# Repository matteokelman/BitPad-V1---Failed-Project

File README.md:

# BitPad-V1---Failed-Project
So this project was meant to be a MacroPad in a retro style with 9 keys and 2 rotary dials, however this was to ambitious for a new hack-clubber with 0 PCB and KiCad knowledge so I am ending the project here to claim my hours of work that went into the project.

Sad to see this project fail but I hope I can do better next time.

Error Report: ** Drc report for MacroPAD.kicad_pcb **
** Created on 2026-10-27T22:11:03 **
** Report includes: Errors, Warnings **
** Found 106 DRC violations **
[shorting_items]: Items shorting two nets (nets Net-(D9-A) and R1)
Local override; error
@(154.7200 mm, 88.9100 mm): Track [Net-(D9-A)] on B.Cu, length 1.9900 mm
@(154.7000 mm, 86.2000 mm): PTH pad 1 [R1] of D1
[shorting_items]: Items shorting two nets (nets Net-(D9-A) and R1)
Local override; error
@(192.8200 mm, 86.9200 mm): Track [Net-(D9-A)] on B.Cu, length 0.0283 mm
@(192.8000 mm, 86.2000 mm): PTH pad 1 [R1] of D3
[shorting_items]: Items shorting two nets (nets R2 and Net-(D9-A))
Local override; error
@(173.7500 mm, 105.2500 mm): PTH pad 1 [R2] of D5
@(173.7700 mm, 105.9700 mm): Track [Net-(D9-A)] on B.Cu, length 0.0283 mm
[shorting_items]: Items shorting two nets (nets R2 and Net-(D9-A))
Local override; error
@(154.7000 mm, 105.2500 mm): PTH pad 1 [R2] of D4
@(154.7200 mm, 107.9600 mm): Track [Net-(D9-A)] on B.Cu, length 1.9900 mm
[shorting_items]: Items shorting two nets (nets R2 and Net-(D9-A))
Local override; error
@(192.8000 mm, 105.2500 mm): PTH pad 1 [R2] of D6
@(192.8200 mm, 107.9600 mm): Track [Net-(D9-A)] on B.Cu, length 1.9900 mm
[shorting_items]: Items shorting two nets (nets Net-(D9-A) and R1)
Local override; error
@(192.8200 mm, 88.9100 mm): Track [Net-(D9-A)] on B.Cu, length 1.9900 mm
@(192.8000 mm, 86.2000 mm): PTH pad 1 [R1] of D3
[shorting_items]: Items shorting two nets (nets R3 and Net-(D9-A))
Local override; error
@(154.7000 mm, 124.3000 mm): PTH pad 1 [R3] of D7
@(154.7200 mm, 125.0200 mm): Track [Net-(D9-A)] on B.Cu, length 0.0283 mm
[shorting_items]: Items shorting two nets (nets R1 and Net-(D9-A))
Local override; error
@(173.7500 mm, 86.2000 mm): PTH pad 1 [R1] of D2
@(173.7700 mm, 86.9200 mm): Track [Net-(D9-A)] on B.Cu, length 0.0283 mm
[shorting_items]: Items shorting two nets (nets R3 and Net-(D9-A))
Local override; error
@(173.7500 mm, 124.3000 mm): PTH pad 1 [R3] of D8
@(173.7700 mm, 127.0100 mm): Track [Net-(D9-A)] on B.Cu, length 1.9900 mm
[shorting_items]: Items shorting two nets (nets Net-(D9-A) and R1)
Local override; error
@(154.7200 mm, 86.9200 mm): Track [Net-(D9-A)] on B.Cu, length 0.0283 mm
@(154.7000 mm, 86.2000 mm): PTH pad 1 [R1] of D1
[shorting_items]: Items shorting two nets (nets R2 and Net-(D9-A))
Local override; error
@(192.8000 mm, 105.2500 mm): PTH pad 1 [R2] of D6
@(192.8200 mm, 105.9700 mm): Track [Net-(D9-A)] on B.Cu, length 0.0283 mm
[shorting_items]: Items shorting two nets (nets Net-(D9-A) and R1)
Local override; error
@(173.7700 mm, 88.9100 mm): Track [Net-(D9-A)] on B.Cu, length 1.9900 mm
@(173.7500 mm, 86.2000 mm): PTH pad 1 [R1] of D2
[shorting_items]: Items shorting two nets (nets R3 and Net-(D9-A))
Local override; error
@(173.7500 mm, 124.3000 mm): PTH pad 1 [R3] of D8
@(173.7700 mm, 125.0200 mm): Track [Net-(D9-A)] on B.Cu, length 0.0283 mm
[shorting_items]: Items shorting two nets (nets Net-(D9-A) and R3)
Local override; error
@(154.7200 mm, 127.0100 mm): Track [Net-(D9-A)] on B.Cu, length 1.9900 mm
@(154.7000 mm, 124.3000 mm): PTH pad 1 [R3] of D7
[shorting_items]: Items shorting two nets (nets Net-(D9-A) and R3)
Local override; error
@(192.8200 mm, 125.0200 mm): Track [Net-(D9-A)] on B.Cu, length 0.0283 mm
@(192.8000 mm, 124.3000 mm): PTH pad 1 [R3] of D9
[shorting_items]: Items shorting two nets (nets R2 and Net-(D9-A))
Local override; error
@(173.7500 mm, 105.2500 mm): PTH pad 1 [R2] of D5
@(173.7700 mm, 107.9600 mm): Track [Net-(D9-A)] on B.Cu, length 1.9900 mm
[shorting_items]: Items shorting two nets (nets R2 and Net-(D9-A))
Local override; error
@(154.7000 mm, 105.2500 mm): PTH pad 1 [R2] of D4
@(154.7200 mm, 105.9700 mm): Track [Net-(D9-A)] on B.Cu, length 0.0283 mm
[shorting_items]: Items shorting two nets (nets Net-(D9-A) and R3)
Local override; error
@(192.8200 mm, 127.0100 mm): Track [Net-(D9-A)] on B.Cu, length 1.9900 mm
@(192.8000 mm, 124.3000 mm): PTH pad 1 [R3] of D9
[copper_edge_clearance]: Board edge clearance violation (board setup constraints edge clearance 0.1500 mm; actual 0.0040 mm)
Rule: board setup constraints edge; error
@(178.8490 mm, 134.9394 mm): Arc of D11 on Edge.Cuts
@(180.1500 mm, 134.5528 mm): Pad 1 [5V] of D11 on B.Cu
[copper_edge_clearance]: Board edge clearance violation (board setup constraints edge clearance 0.1500 mm; actual 0.0040 mm)
Rule: board setup constraints edge; error
@(178.8490 mm, 132.6662 mm): Arc of D11 on Edge.Cuts
@(180.1500 mm, 133.0528 mm): Pad 2 [Net-(D10-DOUT)] of D11 on B.Cu
[copper_edge_clearance]: Board edge clearance violation (board setup constraints edge clearance 0.1500 mm; actual 0.1244 mm)
Rule: board setup constraints edge; error
@(175.3500 mm, 133.1000 mm): Arc of D11 on Edge.Cuts
@(174.9500 mm, 133.0528 mm): Pad 3 [GND] of D11 on B.Cu
[copper_edge_clearance]: Board edge clearance violation (board setup constraints edge clearance 0.1500 mm; actual 0.1244 mm)
Rule: board setup constraints edge; error
@(175.3500 mm, 134.5057 mm): Arc of D11 on Edge.Cuts
@(174.9500 mm, 134.5528 mm): Pad 4 [Net-(D10-DOUT)] of D11 on B.Cu
[copper_edge_clearance]: Board edge clearance violation (board setup constraints edge clearance 0.1500 mm; actual 0.1000 mm)
Rule: board setup constraints edge; error
@(160.2000 mm, 95.0000 mm): Segment of D18 on Edge.Cuts
@(161.1000 mm, 96.4528 mm): Pad 1 [5V] of D18 on B.Cu
[copper_edge_clearance]: Board edge clearance violation (board setup constraints edge clearance 0.1500 mm; actual 0.1000 mm)
Rule: board setup constraints edge; error
@(160.2000 mm, 95.0000 mm): Segment of D18 on Edge.Cuts
@(161.1000 mm, 94.9528 mm): Pad 2 [Net-(D10-DOUT)] of D18 on B.Cu
[copper_edge_clearance]: Board edge clearance violation (board setup constraints edge clearance 0.1500 mm; actual 0.1244 mm)
Rule: board setup constraints edge; error
@(156.3000 mm, 95.0000 mm): Arc of D18 on Edge.Cuts
@(155.9000 mm, 94.9528 mm): Pad 3 [GND] of D18 on B.Cu
[copper_edge_clearance]: Board edge clearance violation (board setup constraints edge clearance 0.1500 mm; actual 0.1000 mm)
Rule: board setup constraints edge; error
@(156.8000 mm, 96.4057 mm): Segment of D18 on Edge.Cuts
@(155.9000 mm, 96.4528 mm): Pad 4 [Net-(D10-DIN)] of D18 on B.Cu
[copper_edge_clearance]: Board edge clearance violation (board setup constraints edge clearance 0.1500 mm; actual 0.1000 mm)
Rule: board setup constraints edge; error
@(198.3000 mm, 133.1000 mm): Segment of D10 on Edge.Cuts
@(199.2000 mm, 134.5528 mm): Pad 1 [5V] of D10 on B.Cu
[copper_edge_clearance]: Board edge clearance violation (board setup constraints edge clearance 0.1500 mm; actual 0.1000 mm)
Rule: board setup constraints edge; error
@(198.3000 mm, 133.1000 mm): Segment of D10 on Edge.Cuts
@(199.2000 mm, 133.0528 mm): Pad 2 [Net-(D10-DOUT)] of D10 on B.Cu
[copper_edge_clearance]: Board edge clearance violation (board setup constraints edge clearance 0.1500 mm; actual 0.1000 mm)
Rule: board setup constraints edge; error
@(194.9000 mm, 134.5057 mm): Segment of D10 on Edge.Cuts
@(194.0000 mm, 133.0528 mm): Pad 3 [GND] of D10 on B.Cu
[copper_edge_clearance]: Board edge clearance violation (board setup constraints edge clearance 0.1500 mm; actual 0.1000 mm)
Rule: board setup constraints edge; error
@(194.9000 mm, 134.5057 mm): Segment of D10 on Edge.Cuts
@(194.0000 mm, 134.5528 mm): Pad 4 [Net-(D10-DOUT)] of D10 on B.Cu
[copper_edge_clearance]: Board edge clearance violation (board setup constraints edge clearance 0.1500 mm; actual 0.1000 mm)
Rule: board setup constraints edge; error
@(156.8000 mm, 115.6000 mm): Segment of D13 on Edge.Cuts
@(155.9000 mm, 114.1472 mm): Pad 1 [5V] of D13 on B.Cu
[copper_edge_clearance]: Board edge clearance violation (board setup constraints edge clearance 0.1500 mm; actual 0.1244 mm)
Rule: board setup constraints edge; error
@(156.3000 mm, 115.6000 mm): Arc of D13 on Edge.Cuts
@(155.9000 mm, 115.6472 mm): Pad 2 [Net-(D10-DOUT)] of D13 on B.Cu
[copper_edge_clearance]: Board edge clearance violation (board setup constraints edge clearance 0.1500 mm; actual 0.0040 mm)
Rule: board setup constraints edge; error
@(159.7990 mm, 116.0338 mm): Arc of D13 on Edge.Cuts
@(161.1000 mm, 115.6472 mm): Pad 3 [GND] of D13 on B.Cu
[copper_edge_clearance]: Board edge clearance violation (board setup constraints edge clearance 0.1500 mm; actual 0.1000 mm)
Rule: board setup constraints edge; error
@(160.2000 mm, 114.1943 mm): Segment of D13 on Edge.Cuts
@(161.1000 mm, 114.1472 mm): Pad 4 [Net-(D10-DOUT)] of D13 on B.Cu
[copper_edge_clearance]: Board edge clearance violation (board setup constraints edge clearance 0.1500 mm; actual 0.0040 mm)
Rule: board setup constraints edge; error
@(197.8990 mm, 96.8394 mm): Arc of D16 on Edge.Cuts
@(199.2000 mm, 96.4528 mm): Pad 1 [5V] of D16 on B.Cu
[copper_edge_clearance]: Board edge clearance violation (board setup constraints edge clearance 0.1500 mm; actual 0.1244 mm)
Rule: board setup constraints edge; error
@(198.8000 mm, 95.0000 mm): Arc of D16 on Edge.Cuts
@(199.2000 mm, 94.9528 mm): Pad 2 [Net-(D10-DOUT)] of D16 on B.Cu
[copper_edge_clearance]: Board edge clearance violation (board setup constraints edge clearance 0.1500 mm; actual 0.0040 mm)
Rule: board setup constraints edge; error
@(195.3010 mm, 94.5662 mm): Arc of D16 on Edge.Cuts
@(194.0000 mm, 94.9528 mm): Pad 3 [GND] of D16 on B.Cu
[copper_edge_clearance]: Board edge clearance violation (board setup constraints edge clearance 0.1500 mm; actual 0.1244 mm)
Rule: board setup constraints edge; error
@(194.4000 mm, 96.4057 mm): Arc of D16 on Edge.Cuts
@(194.0000 mm, 96.4528 mm): Pad 4 [Net-(D10-DOUT)] of D16 on B.Cu
[copper_edge_clearance]: Board edge clearance violation (board setup constraints edge clearance 0.1500 mm; actual 0.0040 mm)
Rule: board setup constraints edge; error
@(159.7990 mm, 134.9394 mm): Arc of D12 on Edge.Cuts
@(161.1000 mm, 134.5528 mm): Pad 1 [5V] of D12 on B.Cu
[copper_edge_clearance]: Board edge clearance violation (board setup constraints edge clearance 0.1500 mm; actual 0.1000 mm)
Rule: board setup constraints edge; error
@(160.2000 mm, 133.1000 mm): Segment of D12 on Edge.Cuts
@(161.1000 mm, 133.0528 mm): Pad 2 [Net-(D10-DOUT)] of D12 on B.Cu
[copper_edge_clearance]: Board edge clearance violation (board setup constraints edge clearance 0.1500 mm; actual 0.1000 mm)
Rule: board setup constraints edge; error
@(156.8000 mm, 134.5057 mm): Segment of D12 on Edge.Cuts
@(155.9000 mm, 133.0528 mm): Pad 3 [GND] of D12 on B.Cu
[copper_edge_clearance]: Board edge clearance violation (board setup constraints edge clearance 0.1500 mm; actual 0.1000 mm)
Rule: board setup constraints edge; error
@(156.8000 mm, 134.5057 mm): Segment of D12 on Edge.Cuts
@(155.9000 mm, 134.5528 mm): Pad 4 [Net-(D10-DOUT)] of D12 on B.Cu
[copper_edge_clearance]: Board edge clearance violation (board setup constraints edge clearance 0.1500 mm; actual 0.0040 mm)
Rule: board setup constraints edge; error
@(178.8490 mm, 96.8394 mm): Arc of D17 on Edge.Cuts
@(180.1500 mm, 96.4528 mm): Pad 1 [5V] of D17 on B.Cu
[copper_edge_clearance]: Board edge clearance violation (board setup constraints edge clearance 0.1500 mm; actual 0.1000 mm)
Rule: board setup constraints edge; error
@(179.2500 mm, 95.0000 mm): Segment of D17 on Edge.Cuts
@(180.1500 mm, 94.9528 mm): Pad 2 [Net-(D10-DOUT)] of D17 on B.Cu
[copper_edge_clearance]: Board edge clearance violation (board setup constraints edge clearance 0.1500 mm; actual 0.1000 mm)
Rule: board setup constraints edge; error
@(175.8500 mm, 96.4057 mm): Segment of D17 on Edge.Cuts
@(174.9500 mm, 94.9528 mm): Pad 3 [GND] of D17 on B.Cu
[copper_edge_clearance]: Board edge clearance violation (board setup constraints edge clearance 0.1500 mm; actual 0.1244 mm)
Rule: board setup constraints edge; error
@(175.3500 mm, 96.4057 mm): Arc of D17 on Edge.Cuts
@(174.9500 mm, 96.4528 mm): Pad 4 [Net-(D10-DOUT)] of D17 on B.Cu
[copper_edge_clearance]: Board edge clearance violation (board setup constraints edge clearance 0.1500 mm; actual 0.1000 mm)
Rule: board setup constraints edge; error
@(194.9000 mm, 115.6000 mm): Segment of D15 on Edge.Cuts
@(194.0000 mm, 114.1472 mm): Pad 1 [5V] of D15 on B.Cu
[copper_edge_clearance]: Board edge clearance violation (board setup constraints edge clearance 0.1500 mm; actual 0.1000 mm)
Rule: board setup constraints edge; error
@(194.9000 mm, 115.6000 mm): Segment of D15 on Edge.Cuts
@(194.0000 mm, 115.6472 mm): Pad 2 [Net-(D10-DOUT)] of D15 on B.Cu
[copper_edge_clearance]: Board edge clearance violation (board setup constraints edge clearance 0.1500 mm; actual 0.0040 mm)
Rule: board setup constraints edge; error
@(197.8990 mm, 116.0338 mm): Arc of D15 on Edge.Cuts
@(199.2000 mm, 115.6472 mm): Pad 3 [GND] of D15 on B.Cu
[copper_edge_clearance]: Board edge clearance violation (board setup constraints edge clearance 0.1500 mm; actual 0.0039 mm)
Rule: board setup constraints edge; error
@(197.8990 mm, 113.7606 mm): Arc of D15 on Edge.Cuts
@(199.2000 mm, 114.1472 mm): Pad 4 [Net-(D10-DOUT)] of D15 on B.Cu
[copper_edge_clearance]: Board edge clearance violation (board setup constraints edge clearance 0.1500 mm; actual 0.0040 mm)
Rule: board setup constraints edge; error
@(176.2510 mm, 113.7606 mm): Arc of D14 on Edge.Cuts
@(174.9500 mm, 114.1472 mm): Pad 1 [5V] of D14 on B.Cu
[copper_edge_clearance]: Board edge clearance violation (board setup constraints edge clearance 0.1500 mm; actual 0.1000 mm)
Rule: board setup constraints edge; error
@(175.8500 mm, 115.6000 mm): Segment of D14 on Edge.Cuts
@(174.9500 mm, 115.6472 mm): Pad 2 [Net-(D10-DOUT)] of D14 on B.Cu
[copper_edge_clearance]: Board edge clearance violation (board setup constraints edge clearance 0.1500 mm; actual 0.1000 mm)
Rule: board setup constraints edge; error
@(179.2500 mm, 114.1943 mm): Segment of D14 on Edge.Cuts
@(180.1500 mm, 115.6472 mm): Pad 3 [GND] of D14 on B.Cu
[copper_edge_clearance]: Board edge clearance violation (board setup constraints edge clearance 0.1500 mm; actual 0.0039 mm)
Rule: board setup constraints edge; error
@(178.8490 mm, 113.7606 mm): Arc of D14 on Edge.Cuts
@(180.1500 mm, 114.1472 mm): Pad 4 [Net-(D10-DOUT)] of D14 on B.Cu
[starved_thermal]: Thermal relief connection to zone incomplete (layer B.Cu; zone min spoke count 2; actual 1)
Local override; error
@(103.0000 mm, 58.0000 mm): Zone [GND] on B.Cu, priority 0
@(161.1000 mm, 115.6472 mm): Pad 3 [GND] of D13 on B.Cu
[starved_thermal]: Thermal relief connection to zone incomplete (layer B.Cu; zone min spoke count 2; actual 1)
Local override; error
@(103.0000 mm, 58.0000 mm): Zone [GND] on B.Cu, priority 0
@(180.1500 mm, 115.6472 mm): Pad 3 [GND] of D14 on B.Cu
[solder_mask_bridge]: Rear solder mask aperture bridges items with different nets
Rule: board setup solder mask min width; error
@(173.7700 mm, 88.9100 mm): Track [Net-(D9-A)] on B.Cu, length 1.9900 mm
@(173.7500 mm, 86.2000 mm): PTH pad 1 [R1] of D2
[solder_mask_bridge]: Rear solder mask aperture bridges items with different nets
Rule: board setup solder mask min width; error
@(192.8200 mm, 127.0100 mm): Track [Net-(D9-A)] on B.Cu, length 1.9900 mm
@(192.8000 mm, 124.3000 mm): PTH pad 1 [R3] of D9
[solder_mask_bridge]: Rear solder mask aperture bridges items with different nets
Rule: board setup solder mask min width; error
@(173.7700 mm, 125.0200 mm): Track [Net-(D9-A)] on B.Cu, length 0.0283 mm
@(173.7500 mm, 124.3000 mm): PTH pad 1 [R3] of D8
[solder_mask_bridge]: Rear solder mask aperture bridges items with different nets
Rule: board setup solder mask min width; error
@(192.8200 mm, 125.0200 mm): Track [Net-(D9-A)] on B.Cu, length 0.0283 mm
@(192.8000 mm, 124.3000 mm): PTH pad 1 [R3] of D9
[solder_mask_bridge]: Rear solder mask aperture bridges items with different nets
Rule: board setup solder mask min width; error
@(154.7200 mm, 88.9100 mm): Track [Net-(D9-A)] on B.Cu, length 1.9900 mm
@(154.7000 mm, 86.2000 mm): PTH pad 1 [R1] of D1
[solder_mask_bridge]: Rear solder mask aperture bridges items with different nets
Rule: board setup solder mask min width; error
@(154.7200 mm, 105.9700 mm): Track [Net-(D9-A)] on B.Cu, length 0.0283 mm
@(154.7000 mm, 105.2500 mm): PTH pad 1 [R2] of D4
[solder_mask_bridge]: Rear solder mask aperture bridges items with different nets
Rule: board setup solder mask min width; error
@(192.8200 mm, 86.9200 mm): Track [Net-(D9-A)] on B.Cu, length 0.0283 mm
@(192.8000 mm, 86.2000 mm): PTH pad 1 [R1] of D3
[solder_mask_bridge]: Rear solder mask aperture bridges items with different nets
Rule: board setup solder mask min width; error
@(173.7700 mm, 107.9600 mm): Track [Net-(D9-A)] on B.Cu, length 1.9900 mm
@(173.7500 mm, 105.2500 mm): PTH pad 1 [R2] of D5
[solder_mask_bridge]: Rear solder mask aperture bridges items with different nets
Rule: board setup solder mask min width; error
@(173.7700 mm, 127.0100 mm): Track [Net-(D9-A)] on B.Cu, length 1.9900 mm
@(173.7500 mm, 124.3000 mm): PTH pad 1 [R3] of D8
[solder_mask_bridge]: Rear solder mask aperture bridges items with different nets
Rule: board setup solder mask min width; error
@(192.8200 mm, 105.9700 mm): Track [Net-(D9-A)] on B.Cu, length 0.0283 mm
@(192.8000 mm, 105.2500 mm): PTH pad 1 [R2] of D6
[solder_mask_bridge]: Rear solder mask aperture bridges items with different nets
Rule: board setup solder mask min width; error
@(154.7200 mm, 127.0100 mm): Track [Net-(D9-A)] on B.Cu, length 1.9900 mm
@(154.7000 mm, 124.3000 mm): PTH pad 1 [R3] of D7
[solder_mask_bridge]: Rear solder mask aperture bridges items with different nets
Rule: board setup solder mask min width; error
@(154.7200 mm, 86.9200 mm): Track [Net-(D9-A)] on B.Cu, length 0.0283 mm
@(154.7000 mm, 86.2000 mm): PTH pad 1 [R1] of D1
[solder_mask_bridge]: Rear solder mask aperture bridges items with different nets
Rule: board setup solder mask min width; error
@(173.7700 mm, 86.9200 mm): Track [Net-(D9-A)] on B.Cu, length 0.0283 mm
@(173.7500 mm, 86.2000 mm): PTH pad 1 [R1] of D2
[solder_mask_bridge]: Rear solder mask aperture bridges items with different nets
Rule: board setup solder mask min width; error
@(192.8200 mm, 88.9100 mm): Track [Net-(D9-A)] on B.Cu, length 1.9900 mm
@(192.8000 mm, 86.2000 mm): PTH pad 1 [R1] of D3
[solder_mask_bridge]: Rear solder mask aperture bridges items with different nets
Rule: board setup solder mask min width; error
@(154.7200 mm, 107.9600 mm): Track [Net-(D9-A)] on B.Cu, length 1.9900 mm
@(154.7000 mm, 105.2500 mm): PTH pad 1 [R2] of D4
[solder_mask_bridge]: Rear solder mask aperture bridges items with different nets
Rule: board setup solder mask min width; error
@(192.8200 mm, 107.9600 mm): Track [Net-(D9-A)] on B.Cu, length 1.9900 mm
@(192.8000 mm, 105.2500 mm): PTH pad 1 [R2] of D6
[solder_mask_bridge]: Rear solder mask aperture bridges items with different nets
Rule: board setup solder mask min width; error
@(154.7200 mm, 125.0200 mm): Track [Net-(D9-A)] on B.Cu, length 0.0283 mm
@(154.7000 mm, 124.3000 mm): PTH pad 1 [R3] of D7
[solder_mask_bridge]: Rear solder mask aperture bridges items with different nets
Rule: board setup solder mask min width; error
@(173.7700 mm, 105.9700 mm): Track [Net-(D9-A)] on B.Cu, length 0.0283 mm
@(173.7500 mm, 105.2500 mm): PTH pad 1 [R2] of D5
[hole_to_hole]: Drilled hole too close to other hole (board setup constraints min 0.2500 mm; actual 0.0000 mm)
Rule: board setup constraints; warning
@(154.7000 mm, 107.7900 mm): PTH pad 2 [Net-(D9-A)] of D4
@(154.7200 mm, 107.9600 mm): PTH pad 2 [Net-(D9-A)] of SW4
[hole_to_hole]: Drilled hole too close to other hole (board setup constraints min 0.2500 mm; actual 0.0000 mm)
Rule: board setup constraints; warning
@(173.7500 mm, 126.8400 mm): PTH pad 2 [Net-(D9-A)] of D8
@(173.7700 mm, 127.0100 mm): PTH pad 2 [Net-(D9-A)] of SW8
[hole_to_hole]: Drilled hole too close to other hole (board setup constraints min 0.2500 mm; actual 0.0000 mm)
Rule: board setup constraints; warning
@(192.8000 mm, 126.8400 mm): PTH pad 2 [Net-(D9-A)] of D9
@(192.8200 mm, 127.0100 mm): PTH pad 2 [Net-(D9-A)] of SW9
[hole_to_hole]: Drilled hole too close to other hole (board setup constraints min 0.2500 mm; actual 0.0000 mm)
Rule: board setup constraints; warning
@(154.7200 mm, 88.9100 mm): PTH pad 2 [Net-(D9-A)] of SW1
@(154.7000 mm, 88.7400 mm): PTH pad 2 [Net-(D9-A)] of D1
[hole_to_hole]: Drilled hole too close to other hole (board setup constraints min 0.2500 mm; actual 0.0000 mm)
Rule: board setup constraints; warning
@(173.7700 mm, 107.9600 mm): PTH pad 2 [Net-(D9-A)] of SW5
@(173.7500 mm, 107.7900 mm): PTH pad 2 [Net-(D9-A)] of D5
[hole_to_hole]: Drilled hole too close to other hole (board setup constraints min 0.2500 mm; actual 0.0000 mm)
Rule: board setup constraints; warning
@(154.7000 mm, 126.8400 mm): PTH pad 2 [Net-(D9-A)] of D7
@(154.7200 mm, 127.0100 mm): PTH pad 2 [Net-(D9-A)] of SW7
[hole_to_hole]: Drilled hole too close to other hole (board setup constraints min 0.2500 mm; actual 0.0000 mm)
Rule: board setup constraints; warning
@(192.8200 mm, 88.9100 mm): PTH pad 2 [Net-(D9-A)] of SW3
@(192.8000 mm, 88.7400 mm): PTH pad 2 [Net-(D9-A)] of D3
[hole_to_hole]: Drilled hole too close to other hole (board setup constraints min 0.2500 mm; actual 0.0000 mm)
Rule: board setup constraints; warning
@(173.7500 mm, 88.7400 mm): PTH pad 2 [Net-(D9-A)] of D2
@(173.7700 mm, 88.9100 mm): PTH pad 2 [Net-(D9-A)] of SW2
[hole_to_hole]: Drilled hole too close to other hole (board setup constraints min 0.2500 mm; actual 0.0000 mm)
Rule: board setup constraints; warning
@(192.8200 mm, 107.9600 mm): PTH pad 2 [Net-(D9-A)] of SW6
@(192.8000 mm, 107.7900 mm): PTH pad 2 [Net-(D9-A)] of D6
[lib_footprint_issues]: The current configuration does not include the footprint library 'footprints'
Local override; warning
@(177.5500 mm, 133.7000 mm): Footprint D11
[lib_footprint_mismatch]: Footprint 'RotaryEncoder_Alps_EC11E-Switch_Vertical_H20mm_CircularMountingHoles' does not match copy in library 'Rotary_Encoder'
Local override; warning
@(175.0000 mm, 77.2500 mm): Footprint SW11
[lib_footprint_issues]: The current configuration does not include the footprint library 'footprints'
Local override; warning
@(158.5000 mm, 95.6000 mm): Footprint D18
[lib_footprint_issues]: The current configuration does not include the footprint library 'footprints'
Local override; warning
@(196.6000 mm, 133.7000 mm): Footprint D10
[lib_footprint_issues]: The current configuration does not include the footprint library 'footprints'
Local override; warning
@(126.0000 mm, 69.0000 mm): Footprint U1
[lib_footprint_issues]: The current configuration does not include the footprint library 'footprints'
Local override; warning
@(158.5000 mm, 115.0000 mm): Footprint D13
[lib_footprint_issues]: The current configuration does not include the footprint library 'footprints'
Local override; warning
@(196.6000 mm, 95.6000 mm): Footprint D16
[lib_footprint_issues]: The current configuration does not include the footprint library 'footprints'
Local override; warning
@(158.5000 mm, 133.7000 mm): Footprint D12
[lib_footprint_issues]: The current configuration does not include the footprint library 'footprints'
Local override; warning
@(177.5500 mm, 95.6000 mm): Footprint D17
[lib_footprint_issues]: The current configuration does not include the footprint library 'footprints'
Local override; warning
@(196.6000 mm, 115.0000 mm): Footprint D15
[lib_footprint_mismatch]: Footprint 'RotaryEncoder_Alps_EC11E-Switch_Vertical_H20mm_CircularMountingHoles' does not match copy in library 'Rotary_Encoder'
Local override; warning
@(194.0000 mm, 77.2500 mm): Footprint SW12
[lib_footprint_issues]: The current configuration does not include the footprint library 'footprints'
Local override; warning
@(177.5500 mm, 115.0000 mm): Footprint D14
[lib_footprint_mismatch]: Footprint 'D_DO-35_SOD27_P2.54mm_Vertical_AnodeUp' does not match copy in library 'Diode_THT'
Local override; warning
@(154.7000 mm, 105.2500 mm): Footprint D4
[lib_footprint_mismatch]: Footprint 'D_DO-35_SOD27_P2.54mm_Vertical_AnodeUp' does not match copy in library 'Diode_THT'
Local override; warning
@(173.7500 mm, 124.3000 mm): Footprint D8
[lib_footprint_mismatch]: Footprint 'D_DO-35_SOD27_P2.54mm_Vertical_AnodeUp' does not match copy in library 'Diode_THT'
Local override; warning
@(154.7000 mm, 124.3000 mm): Footprint D7
[lib_footprint_mismatch]: Footprint 'D_DO-35_SOD27_P2.54mm_Vertical_AnodeUp' does not match copy in library 'Diode_THT'
Local override; warning
@(192.8000 mm, 86.2000 mm): Footprint D3
[lib_footprint_mismatch]: Footprint 'D_DO-35_SOD27_P2.54mm_Vertical_AnodeUp' does not match copy in library 'Diode_THT'
Local override; warning
@(173.7500 mm, 105.2500 mm): Footprint D5
[lib_footprint_mismatch]: Footprint 'D_DO-35_SOD27_P2.54mm_Vertical_AnodeUp' does not match copy in library 'Diode_THT'
Local override; warning
@(192.8000 mm, 105.2500 mm): Footprint D6
[lib_footprint_mismatch]: Footprint 'D_DO-35_SOD27_P2.54mm_Vertical_AnodeUp' does not match copy in library 'Diode_THT'
Local override; warning
@(192.8000 mm, 124.3000 mm): Footprint D9
[lib_footprint_mismatch]: Footprint 'D_DO-35_SOD27_P2.54mm_Vertical_AnodeUp' does not match copy in library 'Diode_THT'
Local override; warning
@(154.7000 mm, 86.2000 mm): Footprint D1
[lib_footprint_mismatch]: Footprint 'D_DO-35_SOD27_P2.54mm_Vertical_AnodeUp' does not match copy in library 'Diode_THT'
Local override; warning
@(173.7500 mm, 86.2000 mm): Footprint D2
[silk_overlap]: Silkscreen clearance (board setup constraints silk clearance 0.1000 mm; actual 0.0000 mm)
Rule: board setup constraints silk; warning
@(121.6000 mm, 129.3000 mm): Reference field of 3.3V
@(121.1000 mm, 128.1000 mm): Segment of GND on F.Silkscreen
[silk_overlap]: Silkscreen clearance (board setup constraints silk clearance 0.1000 mm; actual 0.0000 mm)
Rule: board setup constraints silk; warning
@(121.6000 mm, 129.3000 mm): Reference field of 3.3V
@(121.1000 mm, 130.5000 mm): Segment of GND on F.Silkscreen
** Found 16 unconnected pads **
[unconnected_items]: Missing connection between items
Local override; error
@(154.7200 mm, 125.0200 mm): Track [Net-(D9-A)] on B.Cu, length 0.0283 mm
@(154.7200 mm, 107.9600 mm): PTH pad 2 [Net-(D9-A)] of SW4
[unconnected_items]: Missing connection between items
Local override; error
@(154.7200 mm, 88.9100 mm): PTH pad 2 [Net-(D9-A)] of SW1
@(154.7200 mm, 105.9700 mm): Track [Net-(D9-A)] on B.Cu, length 0.0283 mm
[unconnected_items]: Missing connection between items
Local override; error
@(173.7700 mm, 105.9700 mm): Track [Net-(D9-A)] on B.Cu, length 0.0283 mm
@(154.7200 mm, 107.9600 mm): Track [Net-(D9-A)] on B.Cu, length 1.9900 mm
[unconnected_items]: Missing connection between items
Local override; error
@(173.7700 mm, 88.9100 mm): PTH pad 2 [Net-(D9-A)] of SW2
@(173.7700 mm, 105.9700 mm): Track [Net-(D9-A)] on B.Cu, length 0.0283 mm
[unconnected_items]: Missing connection between items
Local override; error
@(173.7700 mm, 107.9600 mm): PTH pad 2 [Net-(D9-A)] of SW5
@(173.7700 mm, 125.0200 mm): Track [Net-(D9-A)] on B.Cu, length 0.0283 mm
[unconnected_items]: Missing connection between items
Local override; error
@(192.8200 mm, 86.9200 mm): Track [Net-(D9-A)] on B.Cu, length 0.0283 mm
@(173.7700 mm, 88.9100 mm): Track [Net-(D9-A)] on B.Cu, length 1.9900 mm
[unconnected_items]: Missing connection between items
Local override; error
@(192.8200 mm, 105.9700 mm): Track [Net-(D9-A)] on B.Cu, length 0.0283 mm
@(192.8200 mm, 88.9100 mm): PTH pad 2 [Net-(D9-A)] of SW3
[unconnected_items]: Missing connection between items
Local override; error
@(192.8200 mm, 125.0200 mm): Track [Net-(D9-A)] on B.Cu, length 0.0283 mm
@(192.8200 mm, 107.9600 mm): PTH pad 2 [Net-(D9-A)] of SW6
[unconnected_items]: Missing connection between items
Local override; error
@(155.8528 mm, 115.5500 mm): Track [Net-(D10-DOUT)] on B.Cu, length 0.0667 mm
@(161.1000 mm, 114.1472 mm): Pad 4 [Net-(D10-DOUT)] of D13 on B.Cu
[unconnected_items]: Missing connection between items
Local override; error
@(161.1000 mm, 133.0528 mm): Track [Net-(D10-DOUT)] on B.Cu, length 1.5972 mm
@(155.9000 mm, 134.5528 mm): Pad 4 [Net-(D10-DOUT)] of D12 on B.Cu
[unconnected_items]: Missing connection between items
Local override; error
@(174.9500 mm, 96.4528 mm): Pad 4 [Net-(D10-DOUT)] of D17 on B.Cu
@(180.1500 mm, 94.9528 mm): Track [Net-(D10-DOUT)] on B.Cu, length 1.5972 mm
[unconnected_items]: Missing connection between items
Local override; error
@(180.1500 mm, 133.0528 mm): Track [Net-(D10-DOUT)] on B.Cu, length 1.5972 mm
@(174.9500 mm, 134.5528 mm): Pad 4 [Net-(D10-DOUT)] of D11 on B.Cu
[unconnected_items]: Missing connection between items
Local override; error
@(180.1500 mm, 114.1472 mm): Pad 4 [Net-(D10-DOUT)] of D14 on B.Cu
@(174.9028 mm, 115.5500 mm): Track [Net-(D10-DOUT)] on B.Cu, length 0.0667 mm
[unconnected_items]: Missing connection between items
Local override; error
@(194.0000 mm, 96.4528 mm): Pad 4 [Net-(D10-DOUT)] of D16 on B.Cu
@(199.2000 mm, 94.9528 mm): Track [Net-(D10-DOUT)] on B.Cu, length 1.5972 mm
[unconnected_items]: Missing connection between items
Local override; error
@(194.0000 mm, 134.5528 mm): Pad 4 [Net-(D10-DOUT)] of D10 on B.Cu
@(199.2000 mm, 133.0528 mm): Pad 2 [Net-(D10-DOUT)] of D10 on B.Cu
[unconnected_items]: Missing connection between items
Local override; error
@(199.2000 mm, 114.1472 mm): Pad 4 [Net-(D10-DOUT)] of D15 on B.Cu
@(193.9528 mm, 115.5500 mm): Track [Net-(D10-DOUT)] on B.Cu, length 0.0667 mm
** Found 0 Footprint errors **
** Ignored checks **
- Footprint has no courtyard defined
- Track endpoint not centered on via
- Tuning profile track geometries
- Footprint doesn't match symbol's footprint filters
- PTH inside courtyard
- NPTH inside courtyard
- Footprint component type doesn't match footprint pads
** End of Report **

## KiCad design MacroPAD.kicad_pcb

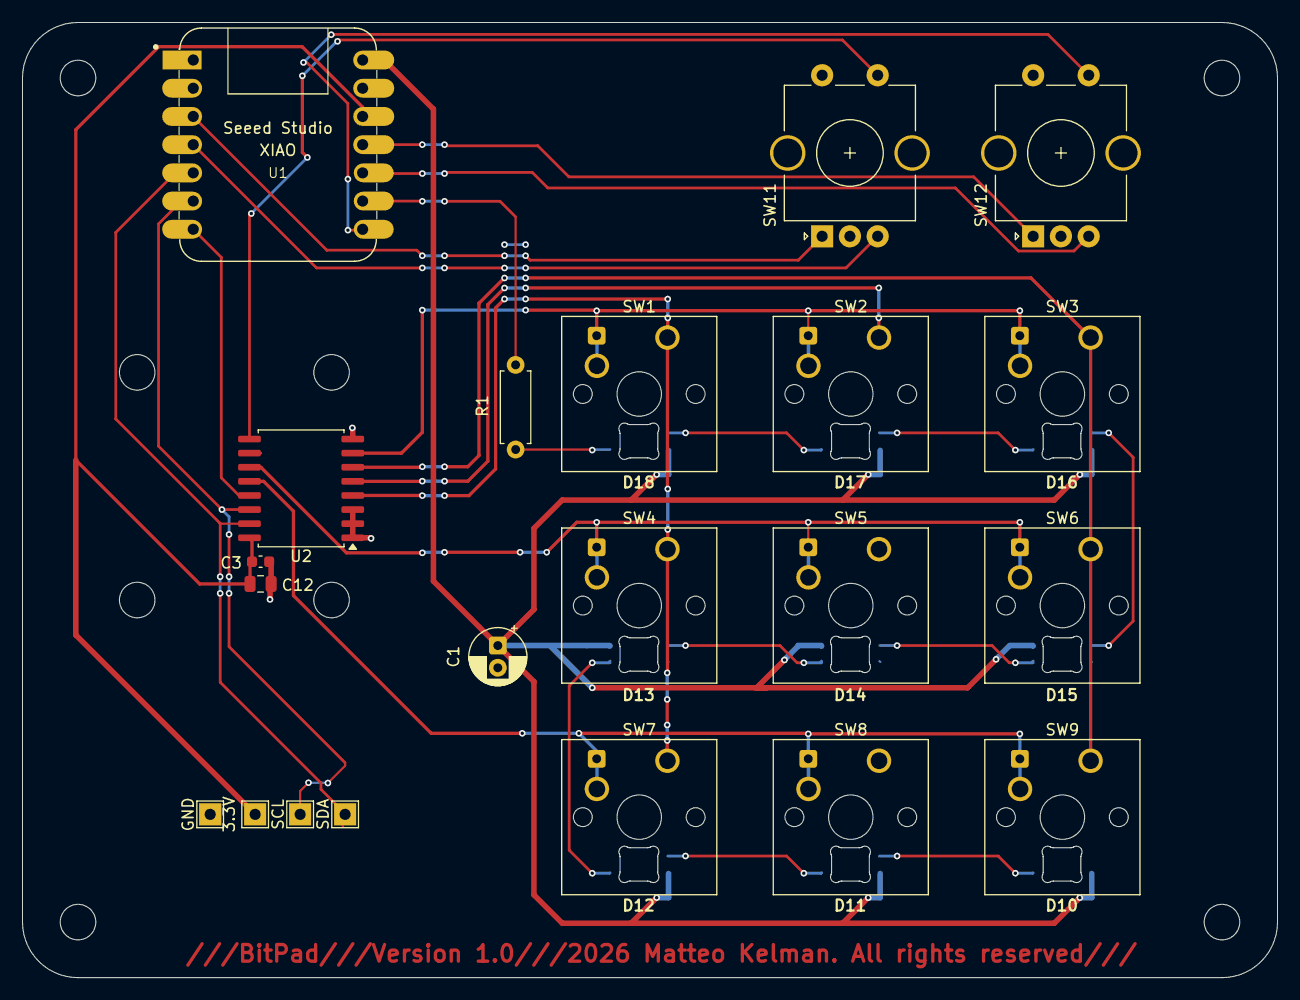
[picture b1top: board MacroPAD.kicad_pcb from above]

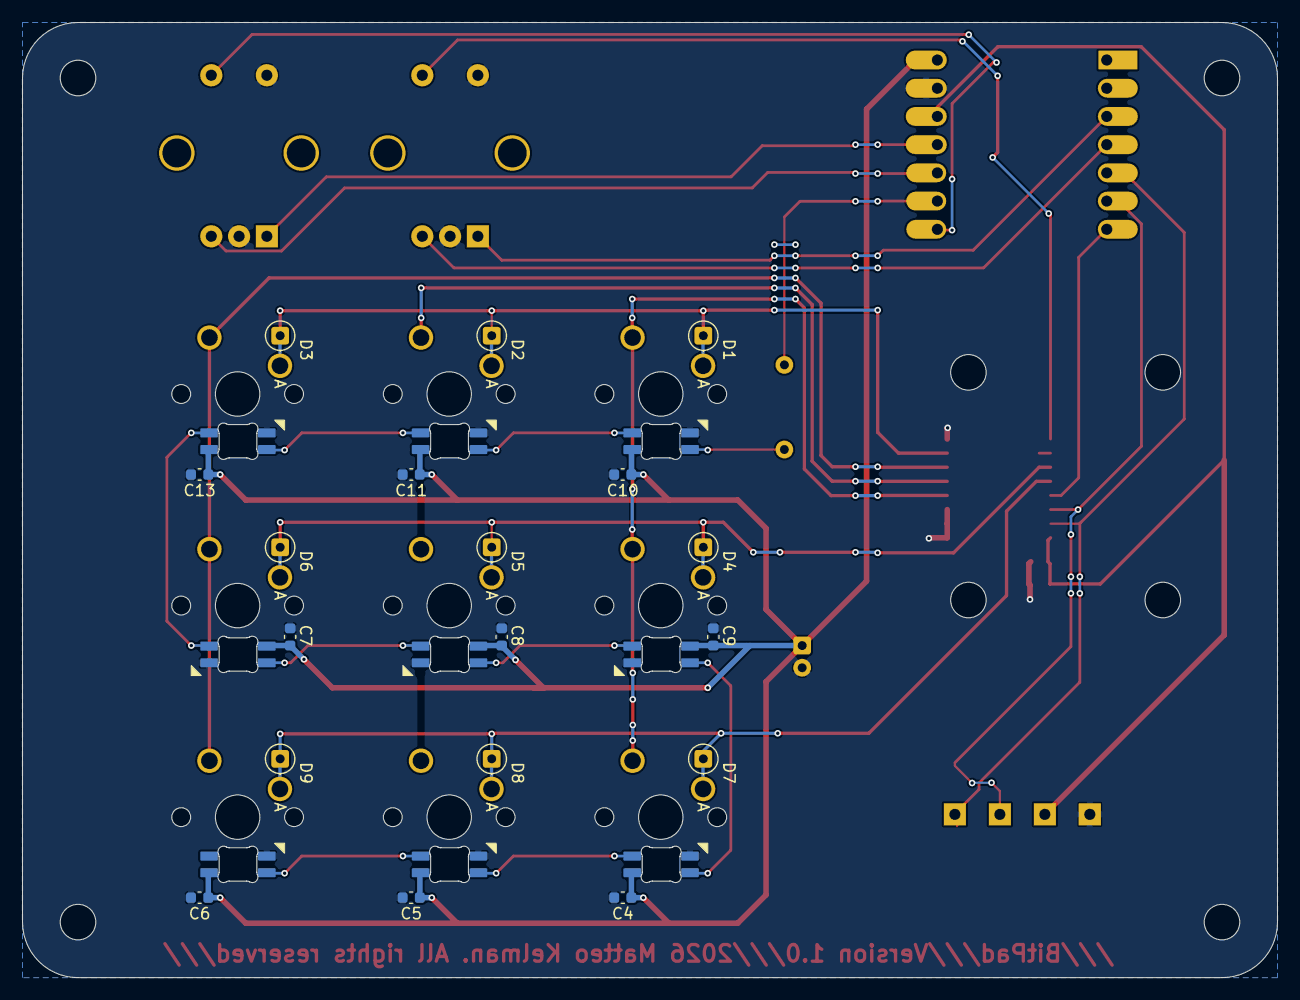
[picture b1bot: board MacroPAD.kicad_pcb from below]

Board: 2 copper layers, 113.0 x 86.0 mm, 48 parts (18 on the bottom side), 22 nets.

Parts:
3.3V: MountingHole_Pad; TestPoint_THTPad_2.0x2.0mm_Drill1.0mm
C1: 47uF; CP_Radial_D5.0mm_P2.00mm
C3, C4, C5, C6, C7, C8, C9, C10, C11, C13: 0.1uF; C_0603_1608Metric
C12: 4.7 µF; C_0805_2012Metric
D1, D2, D3, D4, D5, D6, D7, D8, D9: 1N4148WT; D_DO-35_SOD27_P2.54mm_Vertical_AnodeUp
D10, D11, D12, D13, D14, D15, D16, D17, D18: SK6812MINI-E; SK6812MINI-E_fixed
GND: MountingHole_Pad; TestPoint_THTPad_2.0x2.0mm_Drill1.0mm
R1: 330R; R_Axial_DIN0207_L6.3mm_D2.5mm_P7.62mm_Horizontal
SCL: MountingHole_Pad; TestPoint_THTPad_2.0x2.0mm_Drill1.0mm
SDA: MountingHole_Pad; TestPoint_THTPad_2.0x2.0mm_Drill1.0mm
SW1, SW2, SW3, SW4, SW5, SW6, SW7, SW8, SW9: SW_Push; SW_Cherry_MX_1.00u_PCB
SW11: RotaryEncoder; RotaryEncoder_Alps_EC11E-Switch_Vertical_H20mm_CircularMoun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
SW12: RotaryEncoder_Switch; RotaryEncoder_Alps_EC11E-Switch_Vertical_H20mm_CircularMoun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
U1: MOUDLE-SEEEDUINO-XIAO; XIAO-Generic-Hybrid-14P-2.54-21X17.8MM
U2: PCF8574AT; SOIC-16W_7.5x10.3mm_P1.27mm

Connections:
3.3V: 3.3V.1, C3.1, C12.1, U1.12 (3V3), U2.16 (VDD)
5V: C1.1, C4.1, C5.1, C6.1, C7.1, C8.1, C9.1, C10.1, C11.1, C13.1, D10.1 (VDD), D11.1 (VDD), D12.1 (VDD), D13.1 (VDD), D14.1 (VDD), D15.1 (VDD), D16.1 (VDD), D17.1 (VDD), D18.1 (VDD), U1.14 (5V)
C1: SW1.1, SW4.1, SW7.1, U2.4 (P0)
C2: SW2.1, SW5.1, SW8.1, U2.5 (P1)
C3: SW3.1, SW6.1, SW9.1, U2.6 (P2)
GND: C1.2, C3.2, C4.2, C5.2, C6.2, C7.2, C8.2, C9.2, C10.2, C11.2, C12.2, C13.2, D10.3 (VSS), D11.3 (VSS), D12.3 (VSS), D13.3 (VSS), D14.3 (VSS), D15.3 (VSS), D16.3 (VSS), D17.3 (VSS), D18.3 (VSS), GND.1, SW11.C, SW11.S2, SW12.C, SW12.S2, U1.13 (GND), U2.1 (A0), U2.2 (A1), U2.3 (A2), U2.8 (GND)
INT: U1.7 (PB08_A6_D6_TX), U2.13 (~INT)
Input A2: SW11.A, U1.3 (PA10_A2_D2)
Input A3: SW12.A, U1.11 (PA6_A10_D10_MOSI)
Input B2: SW11.B, U1.4 (PA11_A3_D3)
Input B3: SW12.B, U1.10 (PA5_A9_D9_MISO)
unnamed: D1.2 (A), D2.2 (A), D3.2 (A), D4.2 (A), D5.2 (A), D6.2 (A), D7.2 (A), D8.2 (A), D9.2 (A), SW1.2, SW2.2, SW3.2, SW4.2, SW5.2, SW6.2, SW7.2, SW8.2, SW9.2
unnamed: D18.4 (DIN), R1.2
unnamed: D10.2 (DOUT), D10.4 (DIN), D11.2 (DOUT), D11.4 (DIN), D12.2 (DOUT), D12.4 (DIN), D13.2 (DOUT), D13.4 (DIN), D14.2 (DOUT), D14.4 (DIN), D15.2 (DOUT), D15.4 (DIN), D16.2 (DOUT), D16.4 (DIN), D17.2 (DOUT), D17.4 (DIN), D18.2 (DOUT)
R1: D1.1 (K), D2.1 (K), D3.1 (K), U2.7 (P3)
R2: D4.1 (K), D5.1 (K), D6.1 (K), U2.11 (P6)
R3: D7.1 (K), D8.1 (K), D9.1 (K), U2.12 (P7)
RGB_DATA: R1.1, U1.9 (PA7_A8_D8_SCK)
S1B: SW11.S1B, U2.9 (P4)
S1C: SW12.S1C (S1), U1.8 (PB09_A7_D7_RX)
SCL: SCL.1, U1.6 (PA9_A5_D5_SCL), U2.14 (SCL)
SDA: SDA.1, U1.5 (PA8_A4_D4_SDA), U2.15 (SDA)

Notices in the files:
MacroPAD.kicad_pcb:
BitPad///Version 1.0///2026 Matteo Kelman. All rights reserved
